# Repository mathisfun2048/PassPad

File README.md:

# PassPAD 

## Description and Exigence

This is my fourth attempt at hardware design, and it's been so much fun!

One thing I've been dreading about starting college is moving away from my mac to use a windows laptop for my engineering degree. One of my key contentions was not being able to use the in-built password manger to hold large, secure passwords that I would have otherwise not been able to memorize. This project aims to help me in this problem. 

This device is going to hold passwords with a nickname. The encoder will be able to rotate between saved passwords, with the nickname appearing on the OLED dispaly. The password can be "typed" by repeatedly pressing the switch, which will dynamically change to the charachter next in the password. As a password is being typed, a completion bar will appear on the OLED> After the password is typed, a "completed" message will appear on the oled.

While the hardware for this is pretty simple, the software was not. Instead of being able to use the KMK or QMK frameworks, I learned circuitpython to make this hardware truly custom. I havn't seen a physical password transporter anywhere on the market, so it was really cool building this from scratch. (I submitted it as a 4-point project as my BOM ~$50 , but if you think it may warrent 6 points, please upgrade it :3 )

The design philosophy behind the CAD case for this is similar to my PaperCAM project: I wanted it to be sleek and minimal, in part not to draw attention. This, after all, contains my passwords! I do not want it to be flashy. That's why the case looks quite non-descrcipt. I wanted to add some custimizations, though, so I engraved my logo and a text that reads "PassPad v1". 

In line with keeping things simple (and affordable), I chose a very minimalistic BOM. Here it is below! It is also copied at the end of this README. 

NOTE: I know some items can be found cheaper through other retailars: the only problem is that my parents will only let me buy from the retailors below. If the cost goes above teh allocated cost for my project, I will hapilly pay out of my own pocket. I am grateful to have the opportunity to build this, and I cannot do so if I don't buy the parts from the retailors below.

|Item               |Quantity|Cost |Link                                                                                                                                                                                                                                                                                                                                                                                                                                                                                                                                                         |
|-------------------|--------|-----|-------------------------------------------------------------------------------------------------------------------------------------------------------------------------------------------------------------------------------------------------------------------------------------------------------------------------------------------------------------------------------------------------------------------------------------------------------------------------------------------------------------------------------------------------------------|
|0.91 OLED Display  |1       |5.99 |https://www.amazon.com/gp/product/B08F9F8BYB/ref=ewc_pr_img_3?smid=A3CX4TQNUXMB0L&th=1                                                                                                                                                                                                                                                                                                                                                                                                                                                                       |
|EC11 Rotary Encoder|1       |0 |n/a I should have spares from the Hackpad kit                                                                                                                                                                                                                                                                                                                                                                                                                                                                      |
|MX-Style Switch    |1       |0 |n/a I should have spares from the Hackpad kit                               |
|White DSA Keycap   |1       |0 |n/a I should have spares from the Hackpad kit|
                                                                                                                                            |
|XIAO Microprocessor|1       |9.99 |https://www.amazon.com/gp/product/B09NNVNW7M/ref=ox_sc_act_title_1?smid=A1YP59NGBNBZUR&psc=1                                                                                                                                                                                                                                                                                                                                                                                                                                                                 |
|Custom PCB         |1       |2  + shipping  |https://jlcpcb.com                                                                                                                                                                                                                                                                                                                                                                                                                                                                                                                                           |
|2.5M x 4mm Screws  |8       |0    |n/a, self-provided                                                                                                                                                                                                                                                                                                                                                                                                                                                                                                                                           |
|                   |        |~$38|                                                                                                                                                                                                                                                                                                                                                                                                                                                                                                                                                             |

## Schematic and PCB Design

For this project, I kept pretty much exactly to my initial sketch. Here's some images!

### Schematic

### PCB

## Firmware

Custom firmware! It was super fun to make. If you want a detailed view into my mindset, check out my journal! The runtime script is also included in this repo under the firmware and production directories. 

The code for this project was signficantly longer than teh code for my other projects (being ~600ish lines). I think that's a record for me! I experienced a lot of growth as a dev in this project as I was really able to exercise skills in error handeling and encryption. It was really satisfying to know that the code I have is for a project that I will use rather than something for a test. 

## CAD

The CAD case, like I said above, is simple by design: it is meant to be non-descript so people don't want to steal my passwords (litteraly). Here's some pretty renders of how everything looked at the end. Also, like the PaperCAM, as there is no wiring outside the PCB, no pretty sketch :(. However, I did annotate some of teh images below!

## BOM

NOTE: I know some items can be found cheaper through other retailars: the only problem is that my parents will only let me buy from the retailors below. If the cost goes above teh allocated cost for my project, I will hapilly pay out of my own pocket. I am grateful to have the opportunity to build this, and I cannot do so if I don't buy the parts from the retailors below.

|Item               |Quantity|Cost |Link                                                                                                                                                                                                                                                                                                                                                                                                                                                                                                                                                         |
|-------------------|--------|-----|-------------------------------------------------------------------------------------------------------------------------------------------------------------------------------------------------------------------------------------------------------------------------------------------------------------------------------------------------------------------------------------------------------------------------------------------------------------------------------------------------------------------------------------------------------------|
|0.91 OLED Display  |1       |5.99 |https://www.amazon.com/gp/product/B08F9F8BYB/ref=ewc_pr_img_3?smid=A3CX4TQNUXMB0L&th=1                                                                                                                                                                                                                                                                                                                                                                                                                                                                       |
|EC11 Rotary Encoder|1       |0 |n/a I should have spares from the Hackpad kit                                                                                                                                                                                                                                                                                                                                                                                                                                                                      |
|MX-Style Switch    |1       |0 |n/a I should have spares from the Hackpad kit                               |
|White DSA Keycap   |1       |0 |n/a I should have spares from the Hackpad kit|
                                                                                                                                                                                                                                                                                                                                           |
|XIAO Microprocessor|1       |9.99 |https://www.amazon.com/gp/product/B09NNVNW7M/ref=ox_sc_act_title_1?smid=A1YP59NGBNBZUR&psc=1                                                                                                                                                                                                                                                                                                                                                                                                                                                                 |
|Custom PCB         |1       |2  + shipping  |https://jlcpcb.com                                                                                                                                                                                                                                                                                                                                                                                                                                                                                                                                           |
|2.5M x 4mm Screws  |8       |0    |n/a, self-provided                                                                                                                                                                                                                                                                                                                                                                                                                                                                                                                                           |
|                   |        |~$38|                                                                                                                                                                                                                                                                                                                                                                                                                                                                                                                                                             |

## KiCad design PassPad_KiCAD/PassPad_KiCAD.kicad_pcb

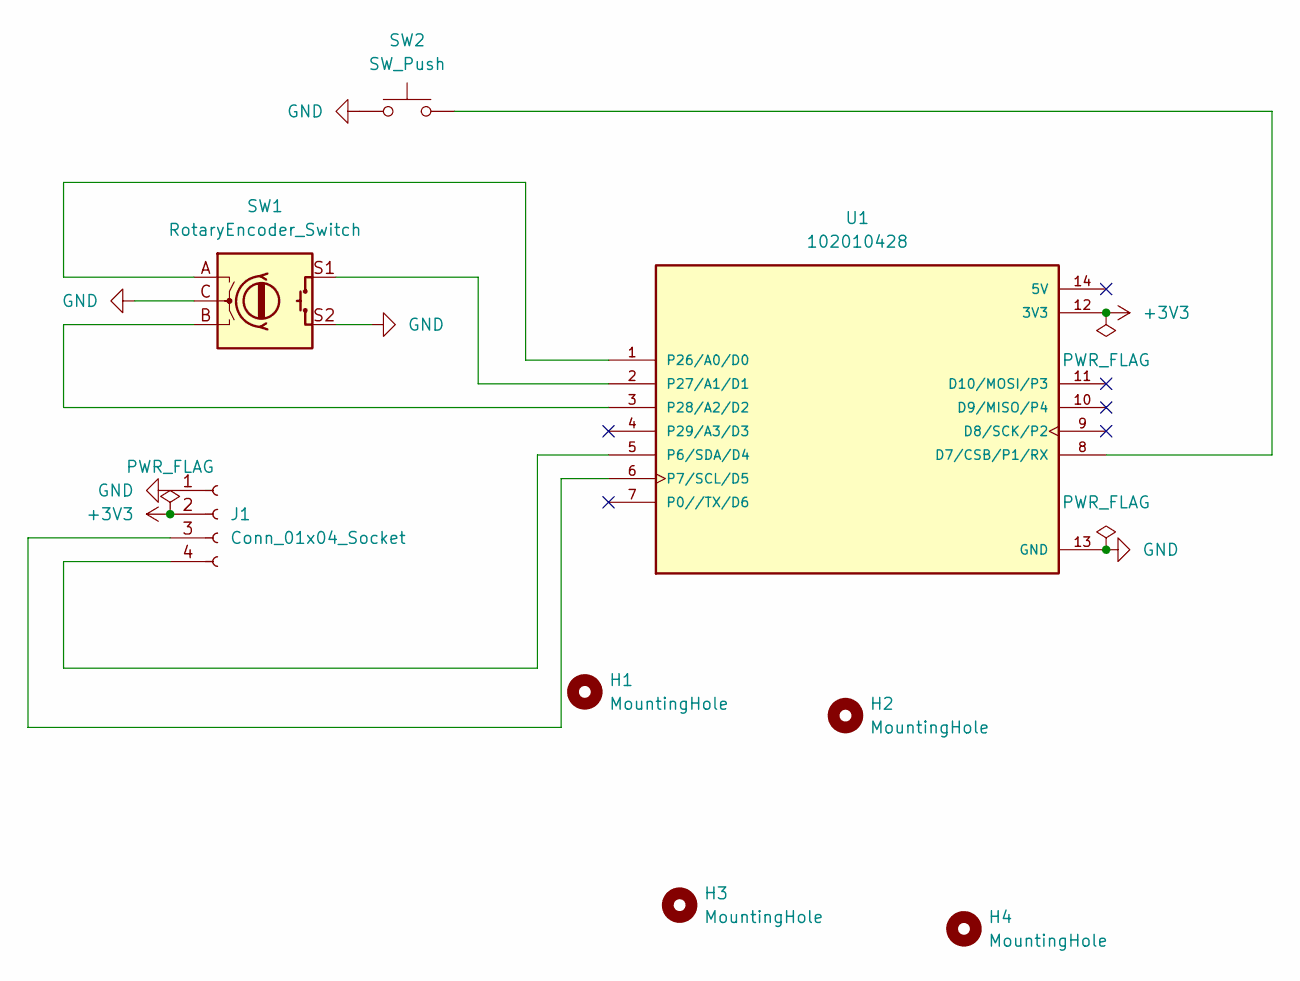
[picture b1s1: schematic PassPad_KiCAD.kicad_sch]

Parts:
H1, H2, H3, H4: MountingHole; MountingHole_2.7mm_M2.5
J1: Conn_01x04_Socket; SSD1306-0.91-OLED-4pin-128x32
SW1: RotaryEncoder_Switch; RotaryEncoder_Alps_EC11E-Switch_Vertical_H20mm
SW2: SW_Push; SW_Cherry_MX_1.00u_PCB
U1: 102010428; XIAO-through-hole; PARTREV 1.3; DigiKey_Part_Number 1597-102010428-ND

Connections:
+3V3: J1.2, U1.12 (3V3)
GND: J1.1, SW1.C, SW1.S2, SW2.1, U1.13 (GND)
unnamed: J1.3, U1.6 (P7/SCL/D5)
unnamed: J1.4, U1.5 (P6/SDA/D4)
unnamed: SW2.2, U1.8 (D7/CSB/P1/RX)
unnamed: SW1.A, U1.1 (P26/A0/D0)
unnamed: SW1.S1, U1.2 (P27/A1/D1)
unnamed: SW1.B, U1.3 (P28/A2/D2)

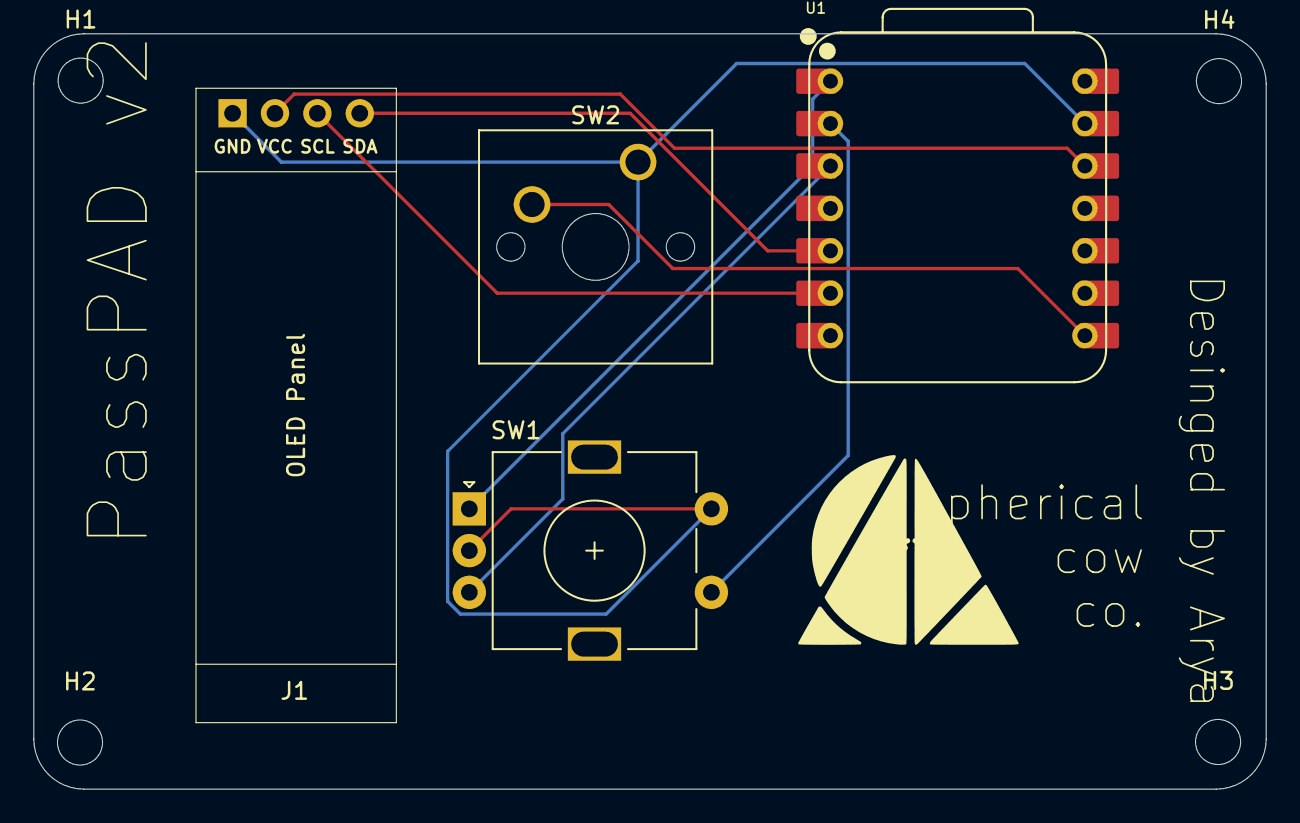
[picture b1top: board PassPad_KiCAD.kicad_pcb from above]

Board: 2 copper layers, 73.8 x 45.2 mm, 8 parts (0 on the bottom side), 8 nets.

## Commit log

2025-06-26 added assets folder and updated journal
2025-06-27 some files
2025-06-27 test
2025-06-27 finished firmware
2025-06-27 added some software stuff
2025-06-27 added some files
2025-07-02 stuff
2025-07-02 fixed PCB mistakes
